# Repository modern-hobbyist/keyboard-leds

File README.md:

# 🎹 Piano Keyboard LED Visualizer (WIP)

This project is a **custom RP2040-based LED controller** designed to add **reactive RGB lighting** to a piano or MIDI keyboard by reading the incoming **MIDI stream** and driving high-density LED strips.

This is my second iteration of MIDI-driven keyboard LEDs, but the first time going *all in* with a fully custom PCB, power-path management, and an onboard touchscreen UI.

⚠️ **Status:** Work in progress  
Hardware is under active development, firmware and features are evolving, and this README will be updated as the project matures.

---

## ✨ High-Level Overview

- Reads **MIDI input** from a keyboard or computer
- Visualizes notes and velocity using **addressable RGB LEDs**
- Includes a **touchscreen UI** for configuring colors, brightness, and animations
- Designed to safely handle **high LED current** while remaining USB-compliant when connected to a computer

The long-term goal is to make this a flexible platform for experimenting with different LED visualization styles while keeping the hardware robust and reusable.

---

## 🔧 Hardware Overview

### Core Components
- **MCU:** RP2040
- **External Flash:** Winbond **W25Q128JVS** (16 MB)
- **Display:** 2.8″ 320×240 TFT LCD with touch
- **LED Support:**  
  - Designed for ~**1–1.5 m of 144 px/m LED strips**
  - Intended for per-key piano illumination

### USB & Power Architecture
- **USB-C (Data / MIDI / Firmware Flashing)**
- **USB-C (Dedicated LED Power Input)**
- **TPS2121** – automatic power-path switching between USB sources
- **TUSB320** – USB-C CC controller used to determine available current
- **Polyfuses** on both USB inputs for protection

The board is designed to intelligently decide how much LED brightness is safe depending on the power source.

---

## 🎯 Design Goals

- **Dual-mode operation**
  - Plugged into a computer → automatically limit LED current to stay within USB limits (~500 mA)
  - Plugged into a keyboard’s MIDI output + external USB-C PSU → allow much higher LED brightness (~3 A target)
- **Touchscreen UI**
  - Adjust brightness, colors, and animations
  - Switch visualization modes without a computer
- **High LED density support**
  - Enough bandwidth and power to drive dense LED strips cleanly
- **Expandable firmware**
  - External flash provides room for animations, fonts, and UI assets

Exact feature set is still evolving — the focus right now is getting the hardware and power logic correct.

---

## 📌 GPIO Pin Map

### SPI Bus — ILI9341 Display + XPT2046 Touch (shared)
| GPIO | Net | Function |
|------|-----|----------|
| 16 | LCD_MISO | SPI MISO |
| 18 | LCD_SCK | SPI clock |
| 19 | LCD_MOSI | SPI MOSI |
| 17 | LCD_CS | ILI9341 chip select |
| 20 | LCD_DC | ILI9341 data/command |
| 21 | LCD_RST | ILI9341 reset |
| 22 | LCD_BL_PWM | Backlight PWM |
| 13 | LCD_T_CS | XPT2046 touch chip select |
| 12 | LCD_T_IRQ | XPT2046 touch interrupt |
| 14 | LCD_SD_CS | SD card chip select (LCD module) |

### I2C Bus — Power Management ICs
| GPIO | Net | Function |
|------|-----|----------|
| 4 | SDA | I2C data (TUSB320) |
| 5 | SCL | I2C clock (TUSB320) |

### LEDs & Power Control
| GPIO | Net | Function |
|------|-----|----------|
| 6 | RGB3.3 | SK6812 data → level shifter → 5 V strip |
| 3 | DIM_DATA | TPS2121 dimming/current limit control |
| 8 | POWER_INT | Interrupt from power management IC |

### USB
| Signal | Function |
|--------|----------|
| USB D+ / D− | Data USB-C — MIDI host + firmware flashing |

### QSPI Flash
Managed automatically by MicroPython. Connected to the W25Q128JVS via the RP2040's dedicated QSPI pins (not accessible as general GPIO).

---

## 🧠 Firmware

MicroPython firmware is included in the `firmware/` directory. See [`firmware/README.md`](firmware/README.md) for full setup and flashing instructions.

**Features:**
- USB MIDI host — keyboard plugs directly into the data USB-C port
- SK6812 LED animations: velocity, rainbow, sustain, single color, gradient
- ILI9341 touchscreen UI with scrollable settings menu
- Persistent settings saved to flash (brightness, animation mode, MIDI channel, LED count, etc.)
- Brightness limiting via TPS2121 `DIM_DATA` line based on available power

**Requirements:** MicroPython ≥ 1.24 for RP2040 with `usb.host` support.

---

## 🧩 PCB Review Context

This board uses a few parts that are new to me, particularly for USB-C and power management:

- **TUSB320** – for USB-C current detection
- **TPS2121** – for seamless power-path switching

While I’ve built multiple custom mechanical keyboards, this is my first design combining:
- Dual USB-C inputs
- High LED current
- USB-compliant behavior
- Onboard display + touch

Feedback on **power logic, USB-C usage, and general robustness** is especially appreciated.

---

## 📦 Bill of Materials (BOM)

A complete BOM is included in the repo and reflects the current PCB revision.  
Key highlights:
- RP2040 MCU
- W25Q128JVS external flash
- TPS2121 power mux
- TUSB320 USB-C controller
- SRV05-4 ESD protection
- TFT LCD (ILI9341-based)

⚠️ Component values and footprints may change as the design is reviewed and iterated.

---

## 📸 Media & Updates

I plan to document this project on my **YouTube channel, Modern Hobbyist**, including:
- PCB bring-up
- Power testing
- LED current experiments
- Firmware development

Links will be added as videos are published.

---

## 🤝 Feedback & Contributions

This repo is currently focused on **design review and learning**, but feedback is very welcome.

If you have experience with:
- USB-C power negotiation
- LED power distribution
- RP2040 display pipelines
- MIDI-driven lighting

…I’d love to hear your thoughts.

---

## 📄 License

TBD (will be added once the design stabilizes)

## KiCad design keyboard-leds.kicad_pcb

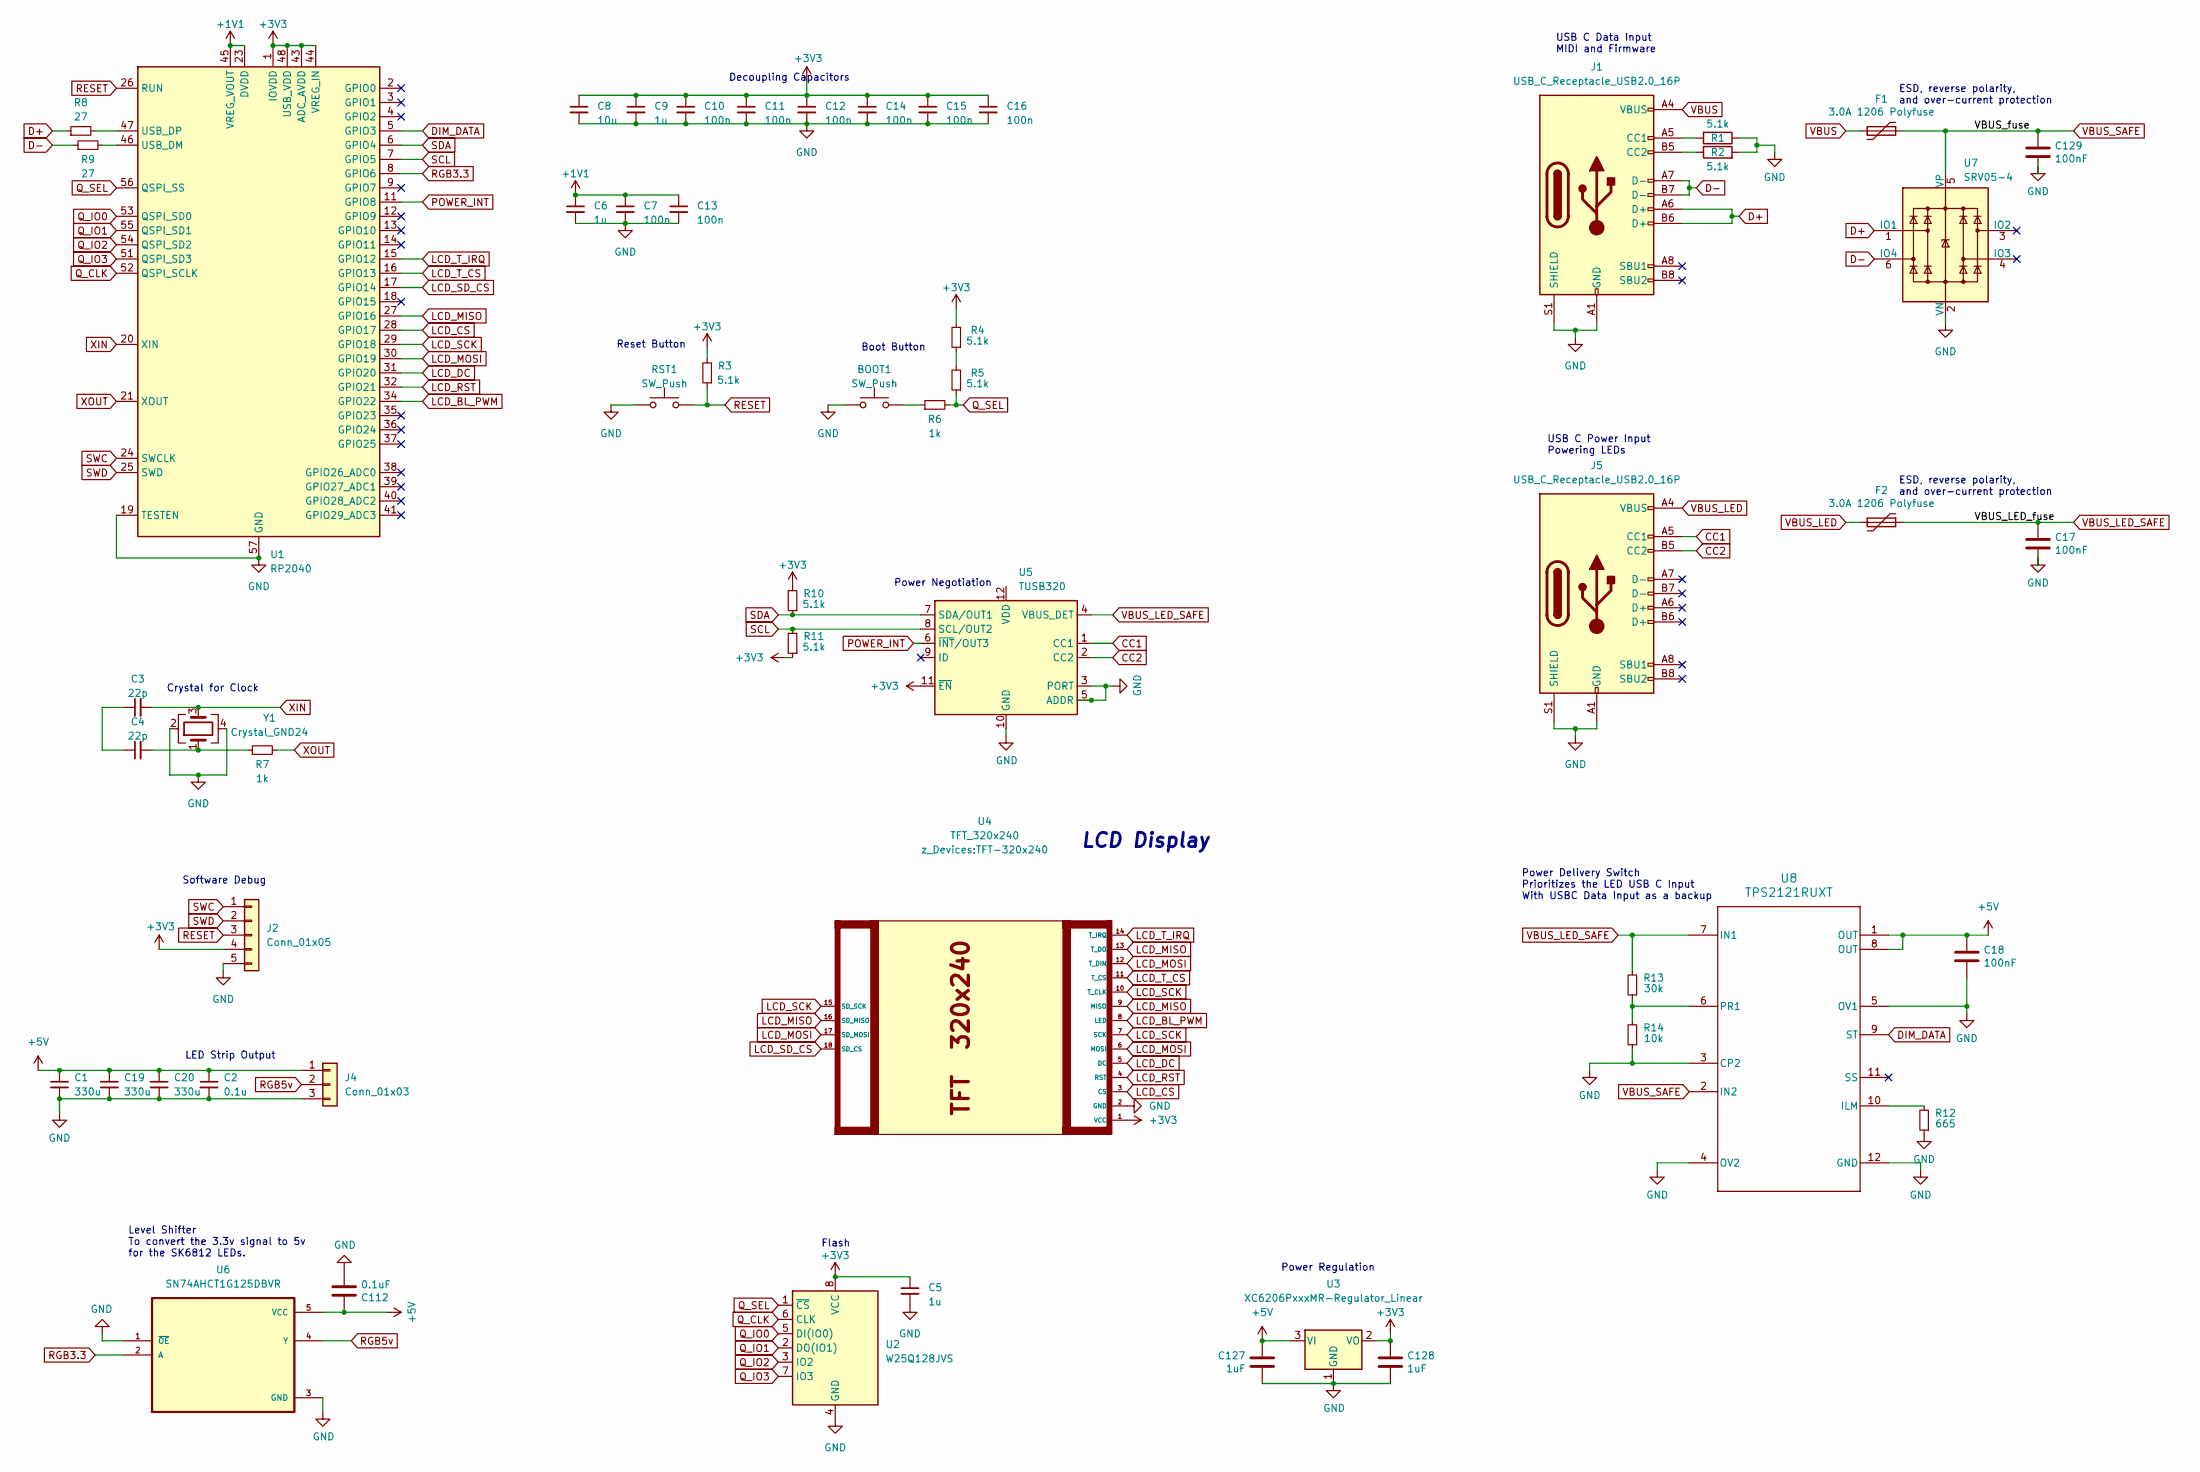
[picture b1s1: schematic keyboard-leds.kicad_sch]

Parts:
BOOT1: SW_Push; SW_SPST_TL3342
C1, C19, C20: 330u; CP_EIA-7343-31_Kemet-D
C2: 0.1u; C_0603_1608Metric
C3, C4: 22p; C_0402_1005Metric
C5, C6, C9: 1u; C_0402_1005Metric
C7, C10, C11, C12, C13, C14, C15, C16: 100n; C_0402_1005Metric
C8: 10u; C_0603_1608Metric
C17, C18, C129: 100nF; C_0402_1005Metric; LCSC C307331
C112: 0.1uF; C_0402_1005Metric; LCSC C307331
C127, C128: 1uF; C_0402_1005Metric; LCSC C307331
F1, F2: 3.0A 1206 Polyfuse; Fuse_1206_3216Metric
J1, J5: USB_C_Receptacle_USB2.0_16P; USB_C_Receptacle_HRO_TYPE-C-31-M-12
J2: Conn_01x05; PinHeader_1x05_P2.54mm_Vertical
J4: Conn_01x03; JST_XH_S3B-XH-A-1_1x03_P2.50mm_Horizontal
R1, R2, R3, R4, R5, R10, R11: 5.1k; R_0402_1005Metric
R6, R7: 1k; R_0402_1005Metric
R8, R9: 27; R_0402_1005Metric
R12: 665; R_0402_1005Metric
R13: 30k; R_0402_1005Metric
R14: 10k; R_0402_1005Metric
RST1: SW_Push; SW_SPST_TL3342
U1: RP2040; QFN-56-1EP_7x7mm_P0.4mm_EP3.2x3.2mm
U2: W25Q128JVS; SOIC-8_5.23x5.23mm_P1.27mm
U3: XC6206PxxxMR-Regulator_Linear; SOT-23; LCSC C5446
U4: TFT_320x240; TFT-320x240
U5: TUSB320; Texas_X2QFN-12_1.6x1.6mm_P0.4mm
U6: SN74AHCT1G125DBVR; SOT95P280X145-5N
U7: SRV05-4; SOT-23-6-routable
U8: TPS2121RUXT; RUX0012A
Y1: Crystal_GND24; Crystal_SMD_3225-4Pin_3.2x2.5mm

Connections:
+1V1: C6.1, C7.1, C13.1, U1.23 (DVDD), U1.45 (VREG_VOUT), U1.50 (DVDD)
+3V3: C5.1, C8.1, C9.1, C10.1, C11.1, C12.1, C14.1, C15.1, C16.1, C128.1, J2.4, R3.2, R4.2, R10.2, R11.1, U1.1 (IOVDD), U1.10 (IOVDD), U1.22 (IOVDD), U1.33 (IOVDD), U1.42 (IOVDD), U1.43 (ADC_AVDD), U1.44 (VREG_IN), U1.48 (USB_VDD), U1.49 (IOVDD), U2.8 (VCC), U3.2 (VO), U4.1 (VCC), U5.11 (~EN)
+5V: C1.1, C2.1, C18.1, C19.1, C20.1, C112.1, C127.1, J4.1, U3.3 (VI), U6.5 (VCC), U8.1 (OUT), U8.8 (OUT)
CC1: J5.A5 (CC1), U5.1 (CC1)
CC2: J5.B5 (CC2), U5.2 (CC2)
D+: J1.A6 (D+), J1.B6 (D+), R8.1, U7.1 (IO1)
D-: J1.A7 (D-), J1.B7 (D-), R9.1, U7.6 (IO4)
DIM_DATA: U1.5 (GPIO3), U8.9 (ST)
GND: BOOT1.1, C1.2, C2.2, C5.2, C6.2, C7.2, C8.2, C9.2, C10.2, C11.2, C12.2, C13.2, C14.2, C15.2, C16.2, C17.2, C18.2, C19.2, C20.2, C112.2, C127.2, C128.2, C129.2, J1.A1 (GND), J1.A12 (GND), J1.B1 (GND), J1.B12 (GND), J1.S1 (SHIELD), J2.5, J4.3, J5.A1 (GND), J5.A12 (GND), J5.B1 (GND), J5.B12 (GND), J5.S1 (SHIELD), R1.1, R2.2, R12.1, R14.1, RST1.1, U1.19 (TESTEN), U1.57 (GND), U2.4 (GND), U3.1 (GND), U4.2 (GND), U5.3 (PORT), U5.5 (ADDR), U5.10 (GND), U6.1 (~OE), U6.3 (GND), U7.2 (VN), U8.3 (CP2), U8.4 (OV2), U8.5 (OV1), U8.12 (GND), Y1.2, Y1.4
LCD_BL_PWM: U1.34 (GPIO22), U4.8 (LED)
LCD_CS: U1.28 (GPIO17), U4.3 (CS)
LCD_DC: U1.31 (GPIO20), U4.5 (DC)
LCD_MISO: U1.27 (GPIO16), U4.9 (MISO), U4.13 (T_DO), U4.16 (SD_MISO)
LCD_MOSI: U1.30 (GPIO19), U4.6 (MOSI), U4.12 (T_DIN), U4.17 (SD_MOSI)
LCD_RST: U1.32 (GPIO21), U4.4 (RST)
LCD_SCK: U1.29 (GPIO18), U4.7 (SCK), U4.10 (T_CLK), U4.15 (SD_SCK)
LCD_SD_CS: U1.17 (GPIO14), U4.18 (SD_CS)
LCD_T_CS: U1.16 (GPIO13), U4.11 (T_CS)
LCD_T_IRQ: U1.15 (GPIO12), U4.14 (T_IRQ)
unnamed: BOOT1.2, R6.1
unnamed: C3.1, C4.1
unnamed: C4.2, R7.1, Y1.1
unnamed: J1.A5 (CC1), R1.2
unnamed: J1.B5 (CC2), R2.1
unnamed: R4.1, R5.2
unnamed: R9.2, U1.46 (USB_DM)
unnamed: R8.2, U1.47 (USB_DP)
unnamed: R12.2, U8.10 (ILM)
unnamed: R13.1, R14.2, U8.6 (PR1)
POWER_INT: U1.11 (GPIO8), U5.6 (~INT/OUT3)
Q_CLK: U1.52 (QSPI_SCLK), U2.6 (CLK)
Q_IO0: U1.53 (QSPI_SD0), U2.5 (DI(IO0))
Q_IO1: U1.55 (QSPI_SD1), U2.2 (DO(IO1))
Q_IO2: U1.54 (QSPI_SD2), U2.3 (IO2)
Q_IO3: U1.51 (QSPI_SD3), U2.7 (IO3)
Q_SEL: R5.1, R6.2, U1.56 (QSPI_SS), U2.1 (~CS)
RESET: J2.3, R3.1, RST1.2, U1.26 (RUN)
RGB3.3: U1.8 (GPIO6), U6.2 (A)
RGB5v: J4.2, U6.4 (Y)
SCL: R11.2, U1.7 (GPIO5), U5.8 (SCL/OUT2)
SDA: R10.1, U1.6 (GPIO4), U5.7 (SDA/OUT1)
SWC: J2.1, U1.24 (SWCLK)
SWD: J2.2, U1.25 (SWD)
VBUS: F1.2, J1.A4 (VBUS), J1.A9 (VBUS), J1.B4 (VBUS), J1.B9 (VBUS)
VBUS_LED: F2.2, J5.A4 (VBUS), J5.A9 (VBUS), J5.B4 (VBUS), J5.B9 (VBUS)
VBUS_LED_SAFE: C17.1, F2.1, R13.2, U5.4 (VBUS_DET), U8.7 (IN1)
VBUS_SAFE: C129.1, F1.1, U7.5 (VP), U8.2 (IN2)
XIN: C3.2, U1.20 (XIN), Y1.3
XOUT: R7.2, U1.21 (XOUT)

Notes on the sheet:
LCD Display
Power Negotiation
Power Delivery Switch Prioritizes the LED USB C Input With USBC Data Input as a backup
Flash
Reset Button
USB C Data Input MIDI and Firmware
LED Strip Output
Crystal for Clock
Decoupling Capacitors
Level Shifter To convert the 3.3v signal to 5v for the SK6812 LEDs.
Boot Button
USB C Power Input Powering LEDs
Software Debug
ESD, reverse polarity, and over-current protection
Power Regulation

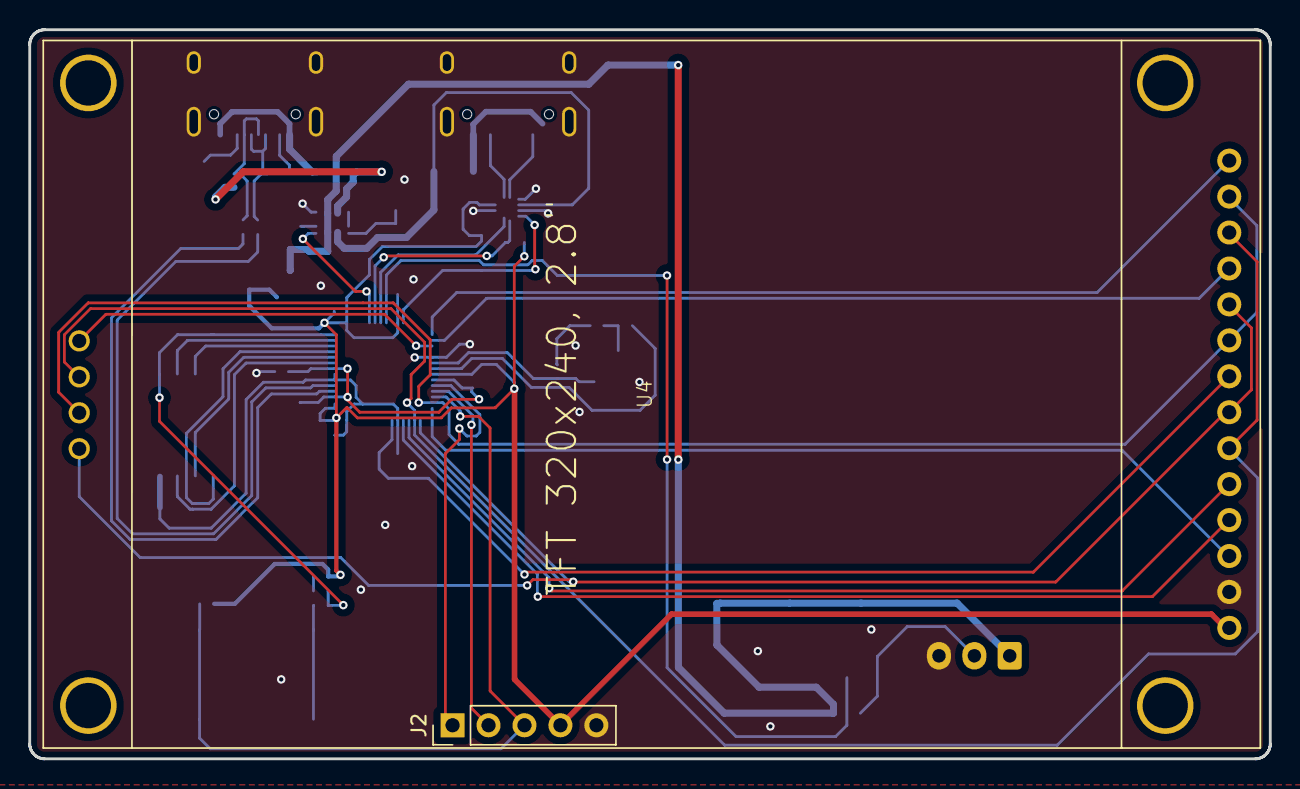
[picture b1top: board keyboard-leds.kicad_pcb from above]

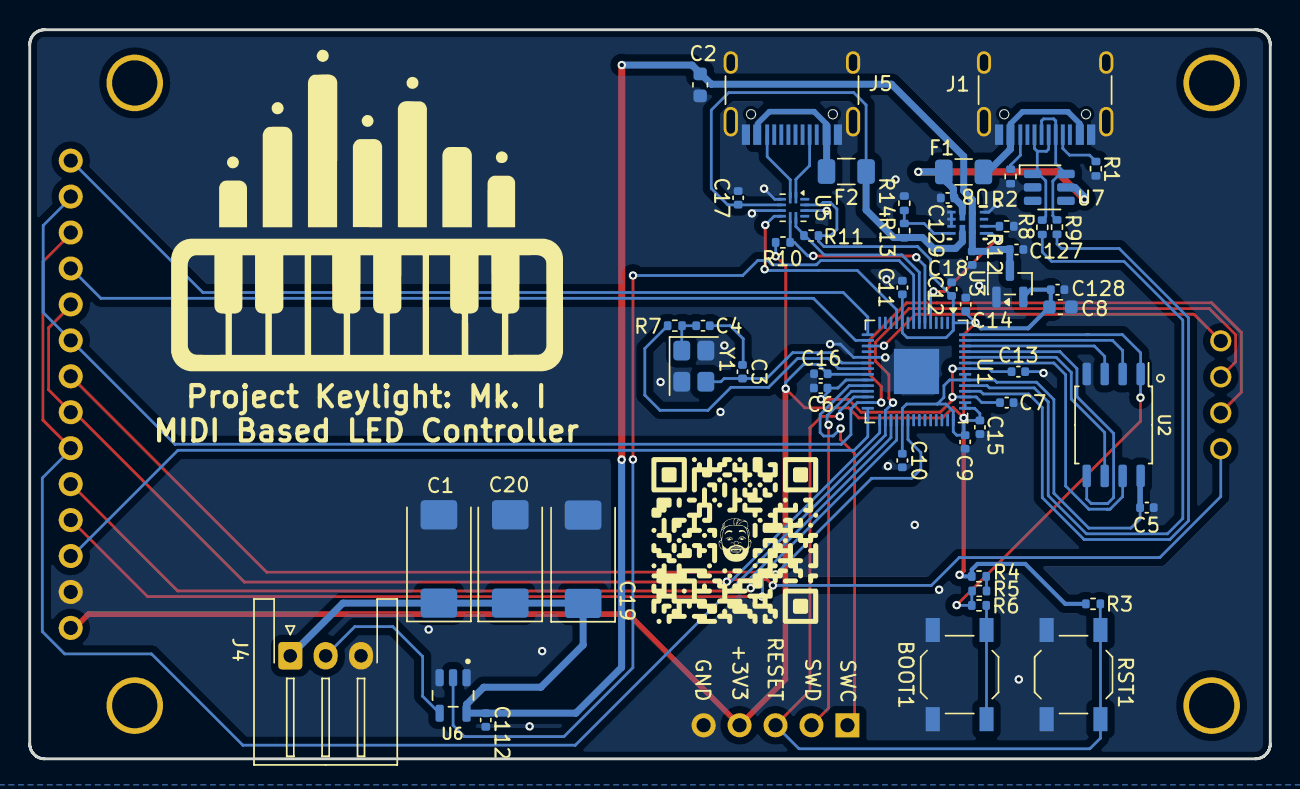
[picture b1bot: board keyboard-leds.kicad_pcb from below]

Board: 2 copper layers, 87.7 x 51.5 mm, 55 parts (53 on the bottom side), 49 nets.

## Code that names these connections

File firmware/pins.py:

# Hardware pin assignments derived from keyboard-leds.kicad_sch
# RP2040 GPIO -> net -> function

# SK6812 LED strip (3.3V data -> level shifter -> 5V -> strip)
LED_DATA = 6          # RGB3.3

# Shared SPI bus (ILI9341 display + XPT2046 touch)
SPI_ID   = 0
SPI_SCK  = 18         # LCD_SCK
SPI_MOSI = 19         # LCD_MOSI
SPI_MISO = 16         # LCD_MISO

# ILI9341 display control
LCD_CS   = 17         # LCD_CS
LCD_DC   = 20         # LCD_DC  (data=1, command=0)
LCD_RST  = 21         # LCD_RST
LCD_BL   = 22         # LCD_BL_PWM  (backlight, PWM on slice 3)

# XPT2046 touch controller (same SPI bus, different CS)
TOUCH_CS  = 13        # LCD_T_CS
TOUCH_IRQ = 12        # LCD_T_IRQ

# SD card on LCD module (reserved, not used)
SD_CS = 14            # LCD_SD_CS

# I2C bus (TUSB320 power negotiation IC)
I2C_ID  = 0
I2C_SDA = 4
I2C_SCL = 5

# Power management
POWER_INT = 8         # Interrupt from power IC
DIM_DATA  = 3         # TPS2121 dimming signal

# MIDI note range for a standard 88-key piano
MIDI_NOTE_MIN = 21    # A0
MIDI_NOTE_MAX = 108   # C8
NUM_PIANO_KEYS = 88

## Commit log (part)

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2025-12-19 Initial work
2025-12-19 Cleaned up board a bit
2025-12-19 Cleaned up footprints
2025-12-19 Added to gitignore
2025-12-20 Fixed footprint again, 3d model and routing
2025-12-20 Wired up SD Card, joined SPI devices
2025-12-20 Added logo and text to PCB
2025-12-23 Moved led output to other side for better cable management
2025-12-23 Added qr code
